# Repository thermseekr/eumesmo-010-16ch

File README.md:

# eumesmo-010-16ch
ESP32 based board with 16x 0-10V analog output, for light dimming control. The board has a DC-DC Converter and an I2C isolator to keep the digital and analog domains fully separated.

The board is compatible with the SP7 DIN rail system from Metaltex.

## VERSION HISTORY
2026-09-22 V1.0 - RJ45 jack and terminal blocks repositioned inwards the board to make space for the PCB holder. ETH tracks rerouted for better EMC.

2026-07-02 V1.0 - Initial release.

## LICENSE

This project is licensed under the [Creative Commons BY-NC 4.0 License](https://creativecommons.org/licenses/by-nc/4.0/).
Commercial use is not permitted without prior written consent. See the [LICENSE.txt](LICENSE.txt) file for details.

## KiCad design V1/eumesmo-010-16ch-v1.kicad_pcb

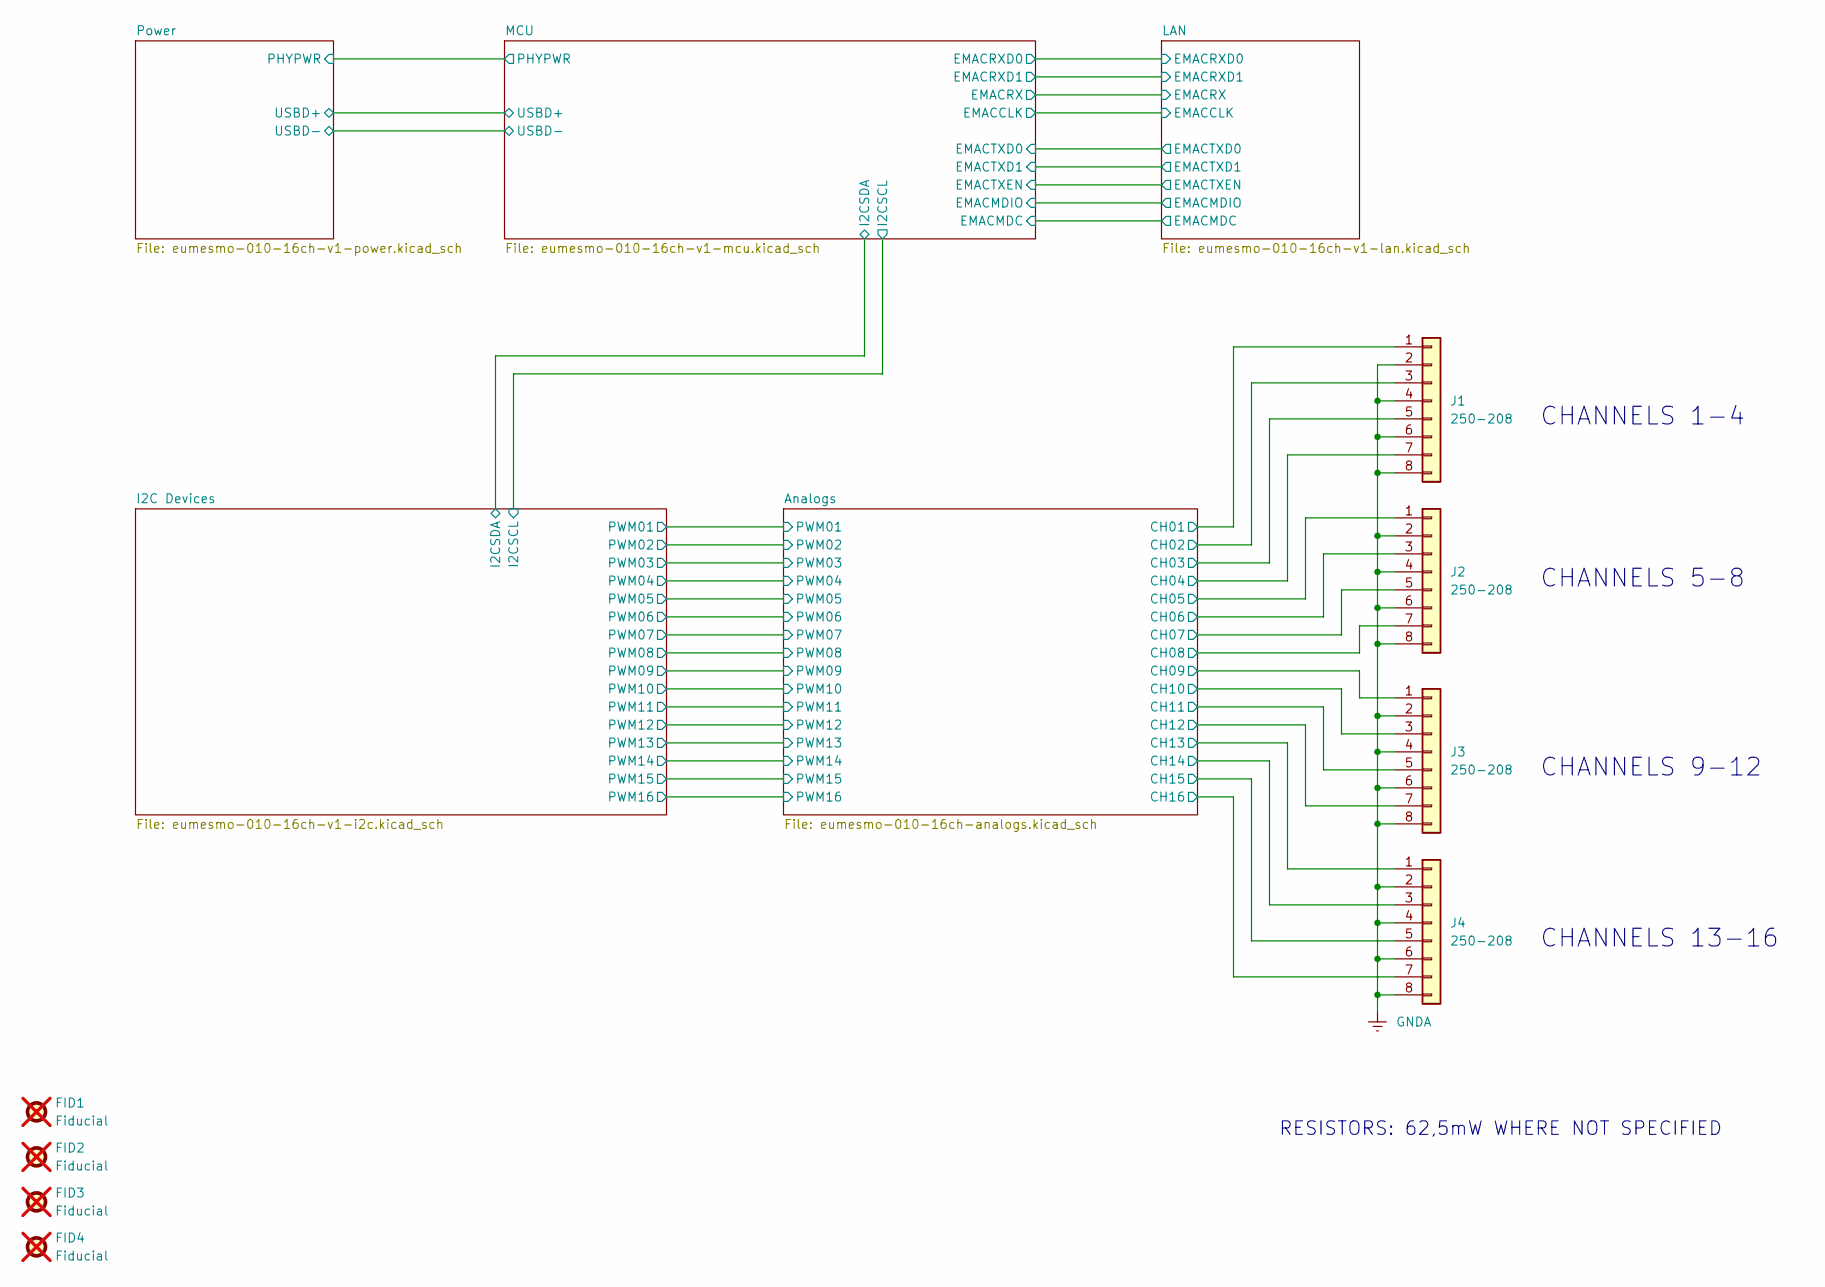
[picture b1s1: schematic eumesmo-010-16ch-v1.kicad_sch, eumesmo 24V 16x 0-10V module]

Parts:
FID1, FID2, FID3, FID4: Fiducial; Fiducial_1mm_Mask2mm; not fitted
J1, J2, J3, J4: 250-208; TerminalBlock_Wago_250-208_1x08_P3.5mm_45Degree; Mfr PN 250-208; LCSC Part # C2833587

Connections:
/Analogs/CH01: J1.1; also elsewhere on the board
/Analogs/CH02: J1.3; also elsewhere on the board
/Analogs/CH03: J1.5; also elsewhere on the board
/Analogs/CH04: J1.7; also elsewhere on the board
/Analogs/CH05: J2.1; also elsewhere on the board
/Analogs/CH06: J2.3; also elsewhere on the board
/Analogs/CH07: J2.5; also elsewhere on the board
/Analogs/CH08: J2.7; also elsewhere on the board
/Analogs/CH09: J3.1; also elsewhere on the board
/Analogs/CH10: J3.3; also elsewhere on the board
/Analogs/CH11: J3.5; also elsewhere on the board
/Analogs/CH12: J3.7; also elsewhere on the board
/Analogs/CH13: J4.1; also elsewhere on the board
/Analogs/CH14: J4.3; also elsewhere on the board
/Analogs/CH15: J4.5; also elsewhere on the board
/Analogs/CH16: J4.7; also elsewhere on the board
GNDA: J1.2, J1.4, J1.6, J1.8, J2.2, J2.4, J2.6, J2.8, J3.2, J3.4, J3.6, J3.8, J4.2, J4.4, J4.6, J4.8; also elsewhere on the board

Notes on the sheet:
CHANNELS 9-12
CHANNELS 13-16
RESISTORS: 62,5mW WHERE NOT SPECIFIED
CHANNELS 1-4
CHANNELS 5-8

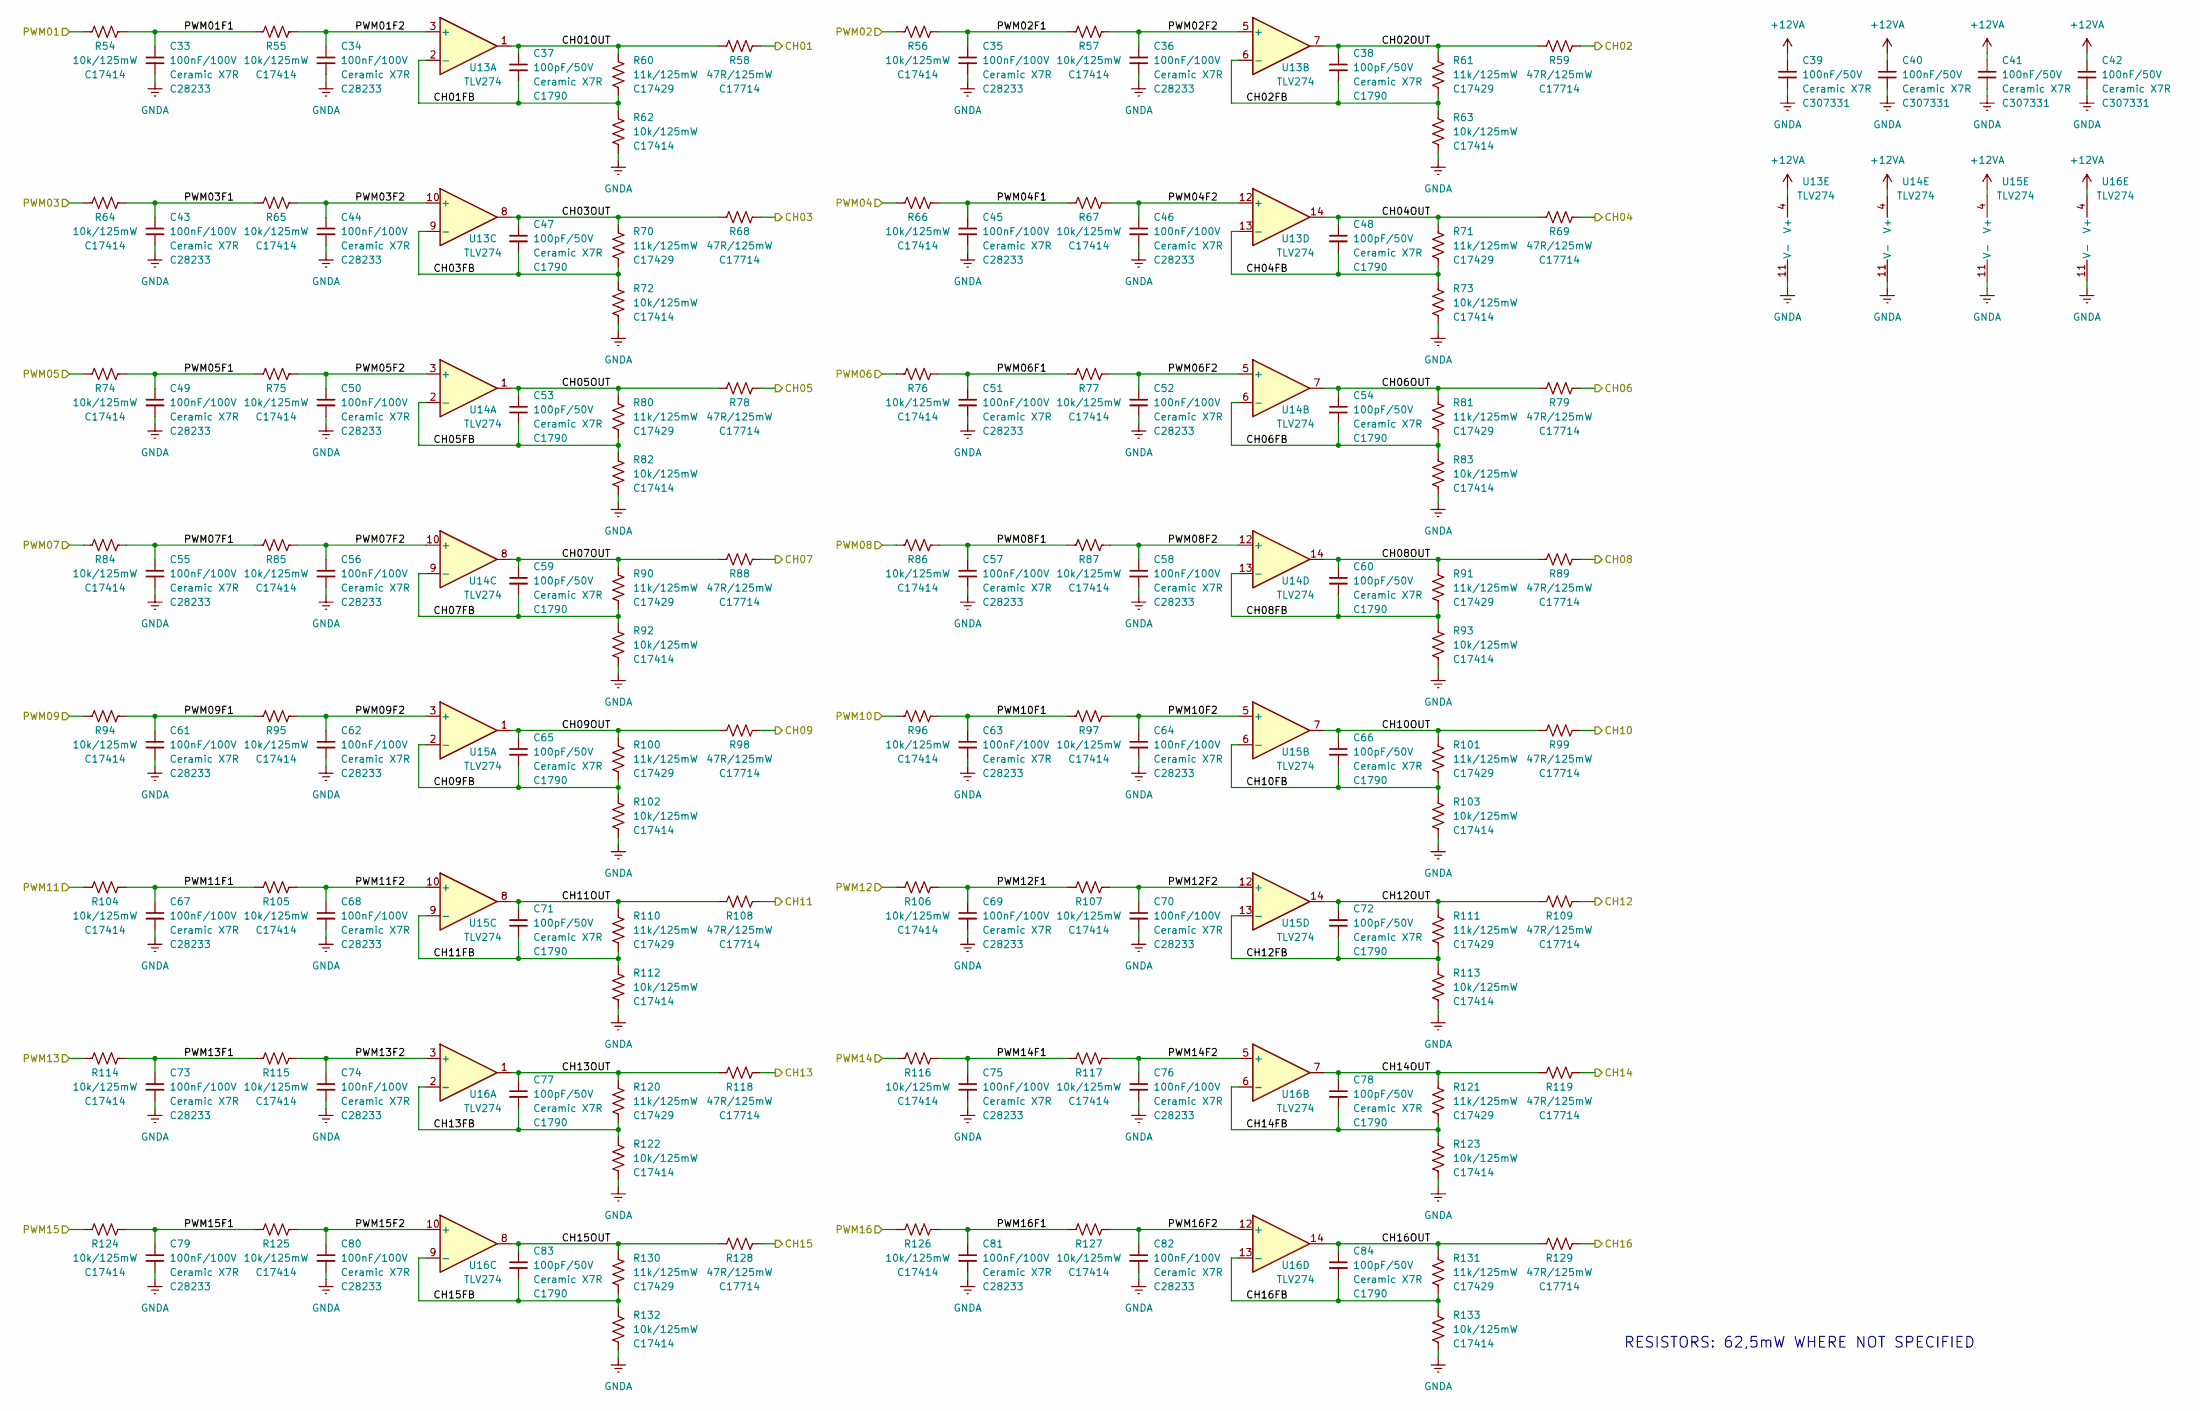
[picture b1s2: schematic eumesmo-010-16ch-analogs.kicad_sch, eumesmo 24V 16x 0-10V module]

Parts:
C33, C34, C35, C36, C43, C44, C45, C46, C49, C50, C51, C52, C55, C56, C57, C58, C61, C62, C63, C64, C67, C68, C69, C70, C73, C74, C75, C76, C79, C80, C81, C82: 100nF/100V; C_0805_2012Metric; Mfr PN CL21B104KCFNNNE; LCSC Part # C28233
C37, C38, C47, C48, C53, C54, C59, C60, C65, C66, C71, C72, C77, C78, C83, C84: 100pF/50V; C_0805_2012Metric; Mfr PN CL21C101JBANNNC; LCSC Part # C1790
C39, C40, C41, C42: 100nF/50V; C_0402_1005Metric; Mfr PN CL05B104KB54PNC; LCSC Part # C307331
R54, R55, R56, R57, R62, R63, R64, R65, R66, R67, R72, R73, R74, R75, R76, R77, R82, R83, R84, R85, R86, R87, R92, R93, R94, R95, R96, R97, R102, R103, R104, R105, R106, R107, R112, R113, R114, R115, R116, R117, R122, R123, R124, R125, R126, R127, R132, R133: 10k/125mW; R_0805_2012Metric; Mfr PN 0805W8F1002T5E; LCSC Part # C17414
R58, R59, R68, R69, R78, R79, R88, R89, R98, R99, R108, R109, R118, R119, R128, R129: 47R/125mW; R_0805_2012Metric; Mfr PN 0805W8F470JT5E; LCSC Part # C17714
R60, R61, R70, R71, R80, R81, R90, R91, R100, R101, R110, R111, R120, R121, R130, R131: 11k/125mW; R_0805_2012Metric; Mfr PN 0805W8F1102T5E; LCSC Part # C17429
U13, U14, U15, U16: TLV274; TSSOP-14_4.4x5mm_P0.65mm; Mfr PN TLV274; LCSC Part # C9914

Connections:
+12VA: C39.1, C40.1, C41.1, C42.1, U13.4 (V+), U14.4 (V+), U15.4 (V+), U16.4 (V+); also elsewhere on the board
/Analogs/CH01: R58.2; also elsewhere on the board
/Analogs/CH01FB: C37.2, R60.1, R62.2, U13.2 (-)
/Analogs/CH01OUT: C37.1, R58.1, R60.2, U13.1
/Analogs/CH02: R59.2; also elsewhere on the board
/Analogs/CH02FB: C38.2, R61.1, R63.2, U13.6 (-)
/Analogs/CH02OUT: C38.1, R59.1, R61.2, U13.7
/Analogs/CH03: R68.2; also elsewhere on the board
/Analogs/CH03FB: C47.2, R70.1, R72.2, U13.9 (-)
/Analogs/CH03OUT: C47.1, R68.1, R70.2, U13.8
/Analogs/CH04: R69.2; also elsewhere on the board
/Analogs/CH04FB: C48.2, R71.1, R73.2, U13.13 (-)
/Analogs/CH04OUT: C48.1, R69.1, R71.2, U13.14
/Analogs/CH05: R78.2; also elsewhere on the board
/Analogs/CH05FB: C53.2, R80.1, R82.2, U14.2 (-)
/Analogs/CH05OUT: C53.1, R78.1, R80.2, U14.1
/Analogs/CH06: R79.2; also elsewhere on the board
/Analogs/CH06FB: C54.2, R81.1, R83.2, U14.6 (-)
/Analogs/CH06OUT: C54.1, R79.1, R81.2, U14.7
/Analogs/CH07: R88.2; also elsewhere on the board
/Analogs/CH07FB: C59.2, R90.1, R92.2, U14.9 (-)
/Analogs/CH07OUT: C59.1, R88.1, R90.2, U14.8
/Analogs/CH08: R89.2; also elsewhere on the board
/Analogs/CH08FB: C60.2, R91.1, R93.2, U14.13 (-)
/Analogs/CH08OUT: C60.1, R89.1, R91.2, U14.14
/Analogs/CH09: R98.2; also elsewhere on the board
/Analogs/CH09FB: C65.2, R100.1, R102.2, U15.2 (-)
/Analogs/CH09OUT: C65.1, R98.1, R100.2, U15.1
/Analogs/CH10: R99.2; also elsewhere on the board
/Analogs/CH10FB: C66.2, R101.1, R103.2, U15.6 (-)
/Analogs/CH10OUT: C66.1, R99.1, R101.2, U15.7
/Analogs/CH11: R108.2; also elsewhere on the board
/Analogs/CH11FB: C71.2, R110.1, R112.2, U15.9 (-)
/Analogs/CH11OUT: C71.1, R108.1, R110.2, U15.8
/Analogs/CH12: R109.2; also elsewhere on the board
/Analogs/CH12FB: C72.2, R111.1, R113.2, U15.13 (-)
/Analogs/CH12OUT: C72.1, R109.1, R111.2, U15.14
/Analogs/CH13: R118.2; also elsewhere on the board
/Analogs/CH13FB: C77.2, R120.1, R122.2, U16.2 (-)
/Analogs/CH13OUT: C77.1, R118.1, R120.2, U16.1
/Analogs/CH14: R119.2; also elsewhere on the board
/Analogs/CH14FB: C78.2, R121.1, R123.2, U16.6 (-)
/Analogs/CH14OUT: C78.1, R119.1, R121.2, U16.7
/Analogs/CH15: R128.2; also elsewhere on the board
/Analogs/CH15FB: C83.2, R130.1, R132.2, U16.9 (-)
/Analogs/CH15OUT: C83.1, R128.1, R130.2, U16.8
/Analogs/CH16: R129.2; also elsewhere on the board
/Analogs/CH16FB: C84.2, R131.1, R133.2, U16.13 (-)
/Analogs/CH16OUT: C84.1, R129.1, R131.2, U16.14
/Analogs/PWM01: R54.1; also elsewhere on the board
/Analogs/PWM01F1: C33.1, R54.2, R55.1
/Analogs/PWM01F2: C34.1, R55.2, U13.3 (+)
/Analogs/PWM02: R56.1; also elsewhere on the board
/Analogs/PWM02F1: C35.1, R56.2, R57.1
/Analogs/PWM02F2: C36.1, R57.2, U13.5 (+)
/Analogs/PWM03: R64.1; also elsewhere on the board
/Analogs/PWM03F1: C43.1, R64.2, R65.1
/Analogs/PWM03F2: C44.1, R65.2, U13.10 (+)
/Analogs/PWM04: R66.1; also elsewhere on the board
/Analogs/PWM04F1: C45.1, R66.2, R67.1
/Analogs/PWM04F2: C46.1, R67.2, U13.12 (+)
/Analogs/PWM05: R74.1; also elsewhere on the board
/Analogs/PWM05F1: C49.1, R74.2, R75.1
/Analogs/PWM05F2: C50.1, R75.2, U14.3 (+)
/Analogs/PWM06: R76.1; also elsewhere on the board
/Analogs/PWM06F1: C51.1, R76.2, R77.1
/Analogs/PWM06F2: C52.1, R77.2, U14.5 (+)
/Analogs/PWM07: R84.1; also elsewhere on the board
/Analogs/PWM07F1: C55.1, R84.2, R85.1
/Analogs/PWM07F2: C56.1, R85.2, U14.10 (+)
/Analogs/PWM08: R86.1; also elsewhere on the board
/Analogs/PWM08F1: C57.1, R86.2, R87.1
/Analogs/PWM08F2: C58.1, R87.2, U14.12 (+)
/Analogs/PWM09: R94.1; also elsewhere on the board
/Analogs/PWM09F1: C61.1, R94.2, R95.1
/Analogs/PWM09F2: C62.1, R95.2, U15.3 (+)
/Analogs/PWM10: R96.1; also elsewhere on the board
/Analogs/PWM10F1: C63.1, R96.2, R97.1
/Analogs/PWM10F2: C64.1, R97.2, U15.5 (+)
/Analogs/PWM11: R104.1; also elsewhere on the board
/Analogs/PWM11F1: C67.1, R104.2, R105.1
/Analogs/PWM11F2: C68.1, R105.2, U15.10 (+)
/Analogs/PWM12: R106.1; also elsewhere on the board
/Analogs/PWM12F1: C69.1, R106.2, R107.1
/Analogs/PWM12F2: C70.1, R107.2, U15.12 (+)
/Analogs/PWM13: R114.1; also elsewhere on the board
/Analogs/PWM13F1: C73.1, R114.2, R115.1
/Analogs/PWM13F2: C74.1, R115.2, U16.3 (+)
/Analogs/PWM14: R116.1; also elsewhere on the board
/Analogs/PWM14F1: C75.1, R116.2, R117.1
/Analogs/PWM14F2: C76.1, R117.2, U16.5 (+)
/Analogs/PWM15: R124.1; also elsewhere on the board
/Analogs/PWM15F1: C79.1, R124.2, R125.1
/Analogs/PWM15F2: C80.1, R125.2, U16.10 (+)
/Analogs/PWM16: R126.1; also elsewhere on the board
/Analogs/PWM16F1: C81.1, R126.2, R127.1
/Analogs/PWM16F2: C82.1, R127.2, U16.12 (+)
GNDA: C33.2, C34.2, C35.2, C36.2, C39.2, C40.2, C41.2, C42.2, C43.2, C44.2, C45.2, C46.2, C49.2, C50.2, C51.2, C52.2, C55.2, C56.2, C57.2, C58.2, C61.2, C62.2, C63.2, C64.2, C67.2, C68.2, C69.2, C70.2, C73.2, C74.2, C75.2, C76.2, C79.2, C80.2, C81.2, C82.2, R62.1, R63.1, R72.1, R73.1, R82.1, R83.1, R92.1, R93.1, R102.1, R103.1, R112.1, R113.1, R122.1, R123.1, R132.1, R133.1, U13.11 (V-), U14.11 (V-), U15.11 (V-), U16.11 (V-); also elsewhere on the board

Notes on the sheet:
RESISTORS: 62,5mW WHERE NOT SPECIFIED

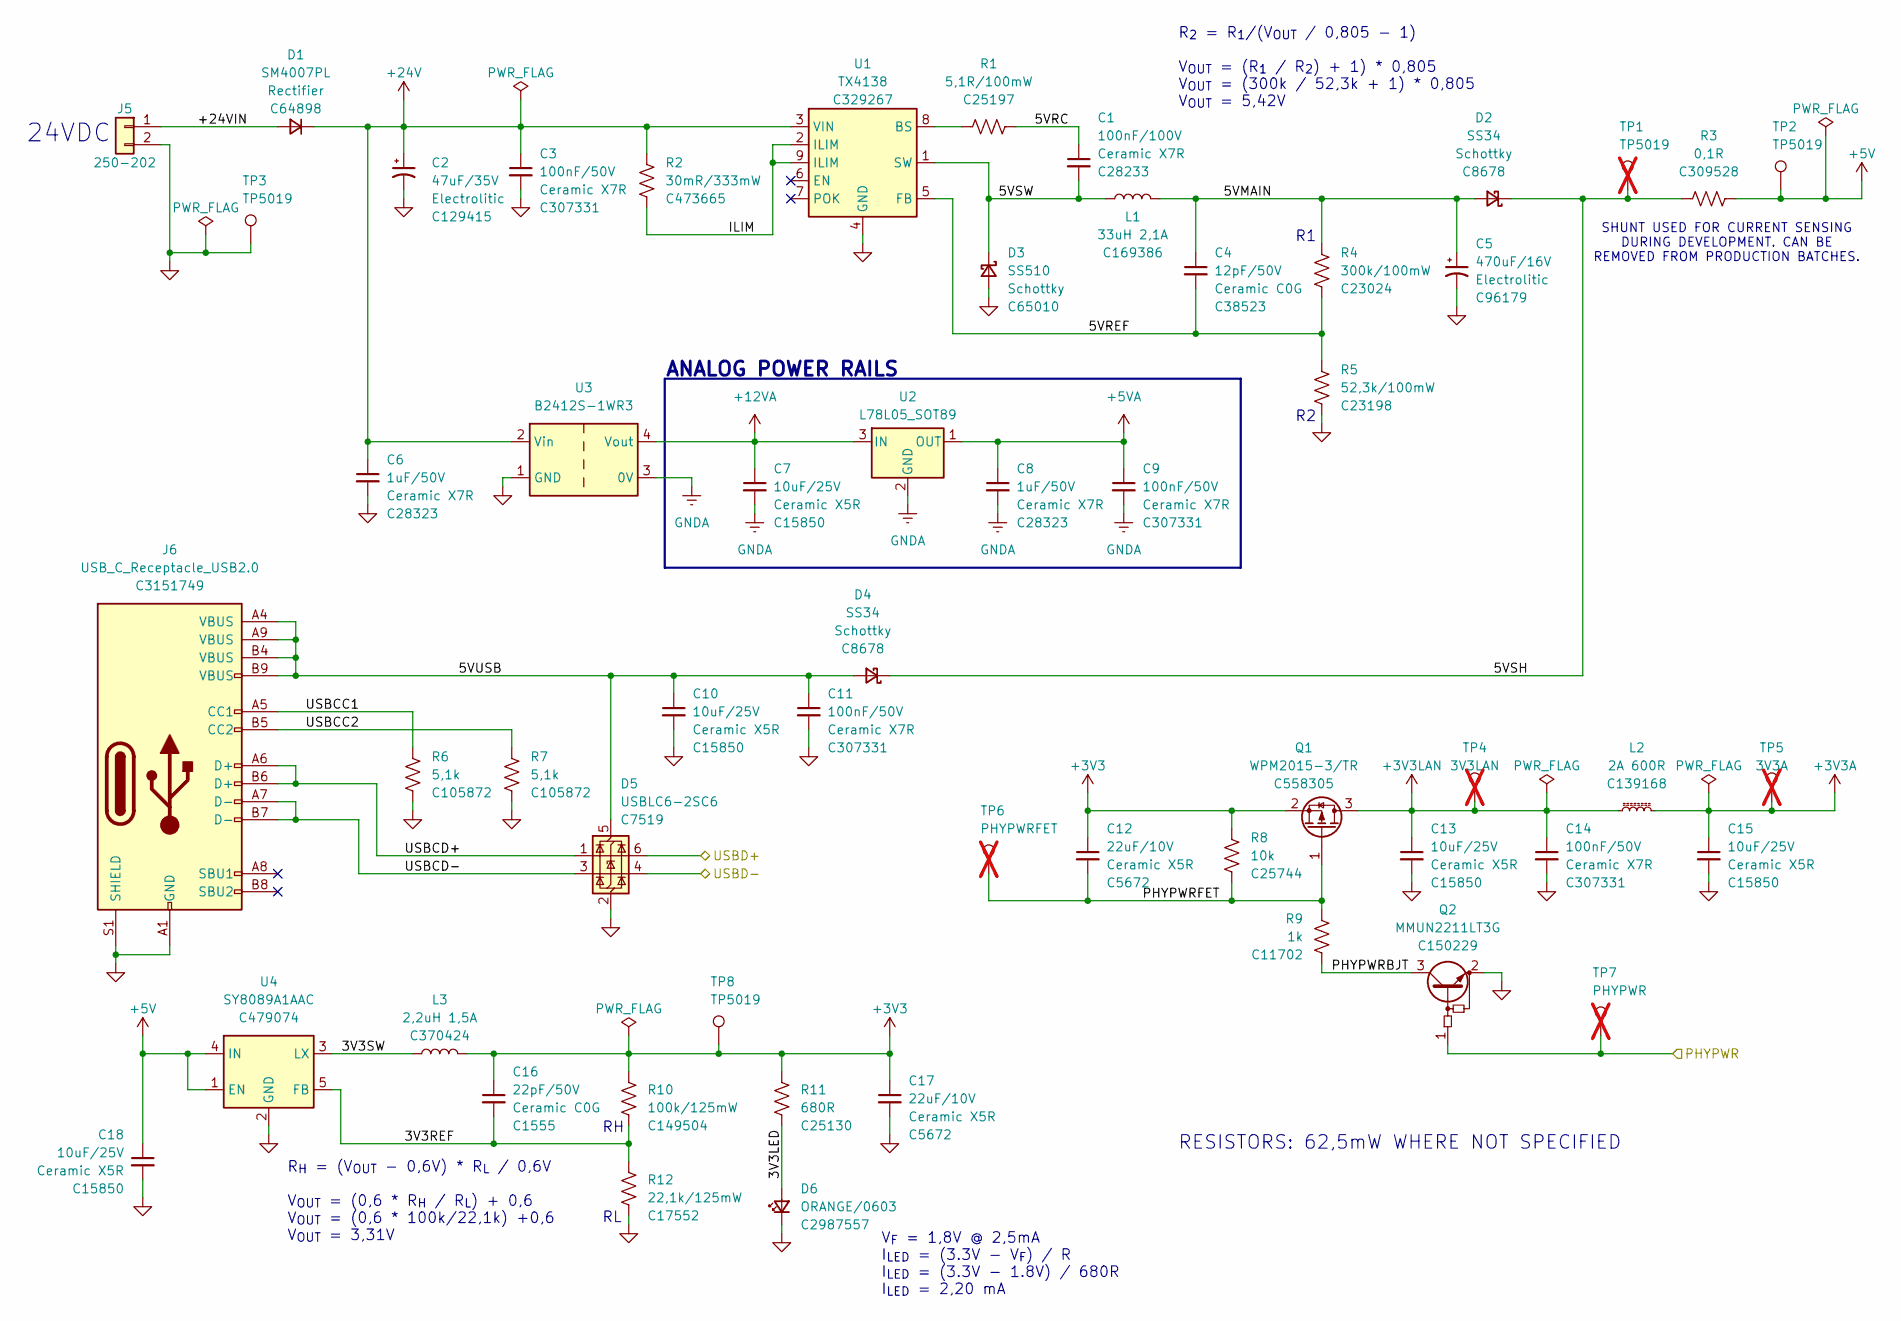
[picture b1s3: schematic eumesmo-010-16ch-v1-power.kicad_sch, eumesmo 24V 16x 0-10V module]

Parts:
C1: 100nF/100V; C_0805_2012Metric; Mfr PN CL21B104KCFNNNE; LCSC Part # C28233
C2: 47uF/35V; CP_Elec_6.3x5.4; Mfr PN CK1V470M-CRE54; LCSC Part # C129415
C3, C9, C11, C14: 100nF/50V; C_0402_1005Metric; Mfr PN CL05B104KB54PNC; LCSC Part # C307331
C4: 12pF/50V; C_0603_1608Metric; Mfr PN CL10C120JB8NNNC; LCSC Part # C38523
C5: 470uF/16V; CP_Elec_8x10.5; Mfr PN CS1C471M-CRF10; LCSC Part # C96179
C6, C8: 1uF/50V; C_0805_2012Metric; Mfr PN CL21B105KBFNNNE; LCSC Part # C28323
C7, C10, C13, C15, C18: 10uF/25V; C_0805_2012Metric; Mfr PN CL21A106KAYNNNE; LCSC Part # C15850
C12, C17: 22uF/10V; C_1206_3216Metric; Mfr PN CL31A226KPHNNNE; LCSC Part # C5672
C16: 22pF/50V; C_0402_1005Metric; Mfr PN 0402CG220J500NT; LCSC Part # C1555
D1: SM4007PL; D_SOD-123; Mfr PN SM4007PL; LCSC Part # C64898
D2, D4: SS34; D_SMA; Mfr PN SS34; LCSC Part # C8678
D3: SS510; D_SMA; Mfr PN SS510; LCSC Part # C65010
D5: USBLC6-2SC6; SOT-23-6; Mfr PN USBLC6-2SC6; LCSC Part # C7519
D6: ORANGE/0603; LED_0603_1608Metric; Mfr PN 19-217/S2C-AL1M2VY/6T; LCSC Part # C2987557
J5: 250-202; TerminalBlock_Wago_250-202_1x02_P3.5mm_45Degree; Mfr PN 250-202; LCSC Part # C2765061
J6: USB_C_Receptacle_USB2.0; USB_C_Receptacle_ShouHan_TYPE-C-16PLT-H10.0; Mfr PN TYPE-C 16PLT-H10.0; LCSC Part # C3151749
L1: 33uH 2,1A; L_12x12mm_H6mm; Mfr PN SWRB1205S-330MT; LCSC Part # C169386
L2: 2A 600R; L_0805_2012Metric; Mfr PN CBM201209U601T; LCSC Part # C139168
L3: 2,2uH 1,5A; L_3x3mm_H1.5mm; Mfr PN SPH3015H2R2MT; LCSC Part # C370424
Q1: WPM2015-3/TR; SOT-23; Mfr PN WPM2015-3/TR; LCSC Part # C558305
Q2: MMUN2211LT3G; SOT-23; Mfr PN MMUN2211LT3G; LCSC Part # C150229
R1: 5,1R/100mW; R_0603_1608Metric; Mfr PN 0603WAF510KT5E; LCSC Part # C25197
R2: 30mR/333mW; R_1206_3216Metric; Mfr PN 1206W3F300MT5E; LCSC Part # C473665
R3: 0,1R; C_1206_3216Metric; Mfr PN PE1206FRF470R1L; LCSC Part # C309528
R4: 300k/100mW; R_0603_1608Metric; Mfr PN 0603WAF3003T5E; LCSC Part # C23024
R5: 52,3k/100mW; R_0603_1608Metric; Mfr PN 0603WAF5232T5E; LCSC Part # C23198
R6, R7: 5,1k; R_0402_1005Metric; Mfr PN RC0402FR-075K1L; LCSC Part # C105872
R8: 10k; R_0402_1005Metric; Mfr PN 0402WGF1002TCE; LCSC Part # C25744
R9: 1k; R_0402_1005Metric; Mfr PN 0402WGF1001TCE; LCSC Part # C11702
R10: 100k/125mW; R_0805_2012Metric; Mfr PN 0805W8F1003T5E; LCSC Part # C149504
R11: 680R; R_0402_1005Metric; Mfr PN 0402WGF6800TCE; LCSC Part # C25130
R12: 22,1k/125mW; R_0805_2012Metric; Mfr PN 0805W8F2212T5E; LCSC Part # C17552
TP1: TP5019; TestPoint_Keystone_5019_Miniature; Mfr PN 5019; LCSC Part # C238131; not fitted
TP2, TP3, TP8: TP5019; TestPoint_Keystone_5019_Miniature; Mfr PN 5019; LCSC Part # C238131
TP4: 3V3LAN; TestPoint_Pad_D1.5mm; not fitted
TP5: 3V3A; TestPoint_Pad_D1.5mm; not fitted
TP6: PHYPWRFET; TestPoint_Pad_D1.5mm; not fitted
TP7: PHYPWR; TestPoint_Pad_D1.5mm; not fitted
U1: TX4138; SOIC-8-1EP_3.9x4.9mm_P1.27mm_EP2.41x3.81mm_ThermalVias; Mfr PN TX4138; LCSC Part # C329267
U2: L78L05_SOT89; SOT-89-3; Mfr PN L78L05ABUTR; LCSC Part # C42738
U3: B2412S-1WR3; Ylptec BxxxxS-1WR3; Mfr PN B2412S-1WR3; LCSC Part # C5369469
U4: SY8089A1AAC; SOT-23-5_Shorter_Pins; Mfr PN SY8089A1AAC; LCSC Part # C479074

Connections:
+3V3: C12.1, C16.1, C17.1, L3.2, Q1.2 (S), R8.1, R10.1, R11.1, TP8.1 (1_1); also elsewhere on the board
+3V3A: C15.1, L2.2, TP5.1; also elsewhere on the board
+3V3LAN: C13.1, C14.1, L2.1, Q1.3 (D), TP4.1; also elsewhere on the board
+5V: C18.1, R3.1, TP2.1 (1_1), U4.1 (EN), U4.4 (IN)
+5VA: C8.1, C9.1, U2.1 (OUT); also elsewhere on the board
+12VA: C7.1, U2.3 (IN), U3.4 (Vout); also elsewhere on the board
+24V: C2.1, C3.1, C6.1, D1.1 (K), R2.1, U1.3 (VIN), U3.2 (Vin)
/MCU/PHYPWR: Q2.1 (B), TP7.1; also elsewhere on the board
/MCU/USBD+: D5.6 (I/O1); also elsewhere on the board
/MCU/USBD-: D5.4 (I/O2); also elsewhere on the board
/Power/3V3LED: D6.2 (A), R11.2
/Power/3V3REF: C16.2, R10.2, R12.1, U4.5 (FB)
/Power/3V3SW: L3.1, U4.3 (LX)
/Power/5VMAIN: C4.1, C5.1, D2.2 (A), L1.2, R4.1
/Power/5VRC: C1.1, R1.1
/Power/5VREF: C4.2, R4.2, R5.1, U1.5 (FB)
/Power/5VSH: D2.1 (K), D4.1 (K), R3.2, TP1.1
/Power/5VSW: C1.2, D3.1 (K), L1.1, U1.1 (SW)
/Power/5VUSB: C10.1, C11.1, D4.2 (A), D5.5 (VBUS), J6.A4 (VBUS), J6.A9 (VBUS), J6.B4 (VBUS), J6.B9 (VBUS)
/Power/+24VIN: D1.2 (A), J5.1
/Power/ILIM: R2.2, U1.2 (ILIM), U1.9 (ILIM)
/Power/PHYPWRBJT: Q2.3 (C), R9.1
/Power/PHYPWRFET: C12.2, Q1.1 (G), R8.2, R9.2, TP6.1
/Power/USBCC1: J6.A5 (CC1), R6.1
/Power/USBCC2: J6.B5 (CC2), R7.1
/Power/USBCD+: D5.1 (I/O1), J6.A6 (D+), J6.B6 (D+)
/Power/USBCD-: D5.3 (I/O2), J6.A7 (D-), J6.B7 (D-)
GND: C2.2, C3.2, C5.2, C6.2, C10.2, C11.2, C13.2, C14.2, C15.2, C17.2, C18.2, D3.2 (A), D5.2 (GND), D6.1 (K), J5.2, J6.A1 (GND), J6.A12 (GND), J6.B1 (GND), J6.B12 (GND), J6.S1 (SHIELD), Q2.2 (E), R5.2, R6.2, R7.2, R12.2, TP3.1 (1_1), U1.4 (GND), U3.1 (GND), U4.2 (GND); also elsewhere on the board
GNDA: C7.2, C8.2, C9.2, U2.2 (GND), U3.3 (0V); also elsewhere on the board
unnamed: R1.2, U1.8 (BS)

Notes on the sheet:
RESISTORS: 62,5mW WHERE NOT SPECIFIED
R_{H} = (V_{OUT} - 0,6V) * R_{L} / 0,6V V_{OUT} = (0,6 * R_{H} / R_{L}) + 0,6 V_{OUT} = (0,6 * 100k/22,1k) +0,6 V_{OUT} = 3,31V
R_{2} = R_{1}/(V_{OUT} / 0,805 - 1) V_{OUT} = (R_{1} / R_{2}) + 1) * 0,805 V_{OUT} = (300k / 52,3k + 1) * 0,805 V_{OUT} = 5,42V
SHUNT USED FOR CURRENT SENSING DURING DEVELOPMENT. CAN BE REMOVED FROM PRODUCTION BATCHES.
V_{F} = 1,8V @ 2,5mA I_{LED} = (3.3V - V_{F}) / R I_{LED} = (3.3V - 1.8V) / 680R I_{LED} = 2,20 mA
ANALOG POWER RAILS
24VDC

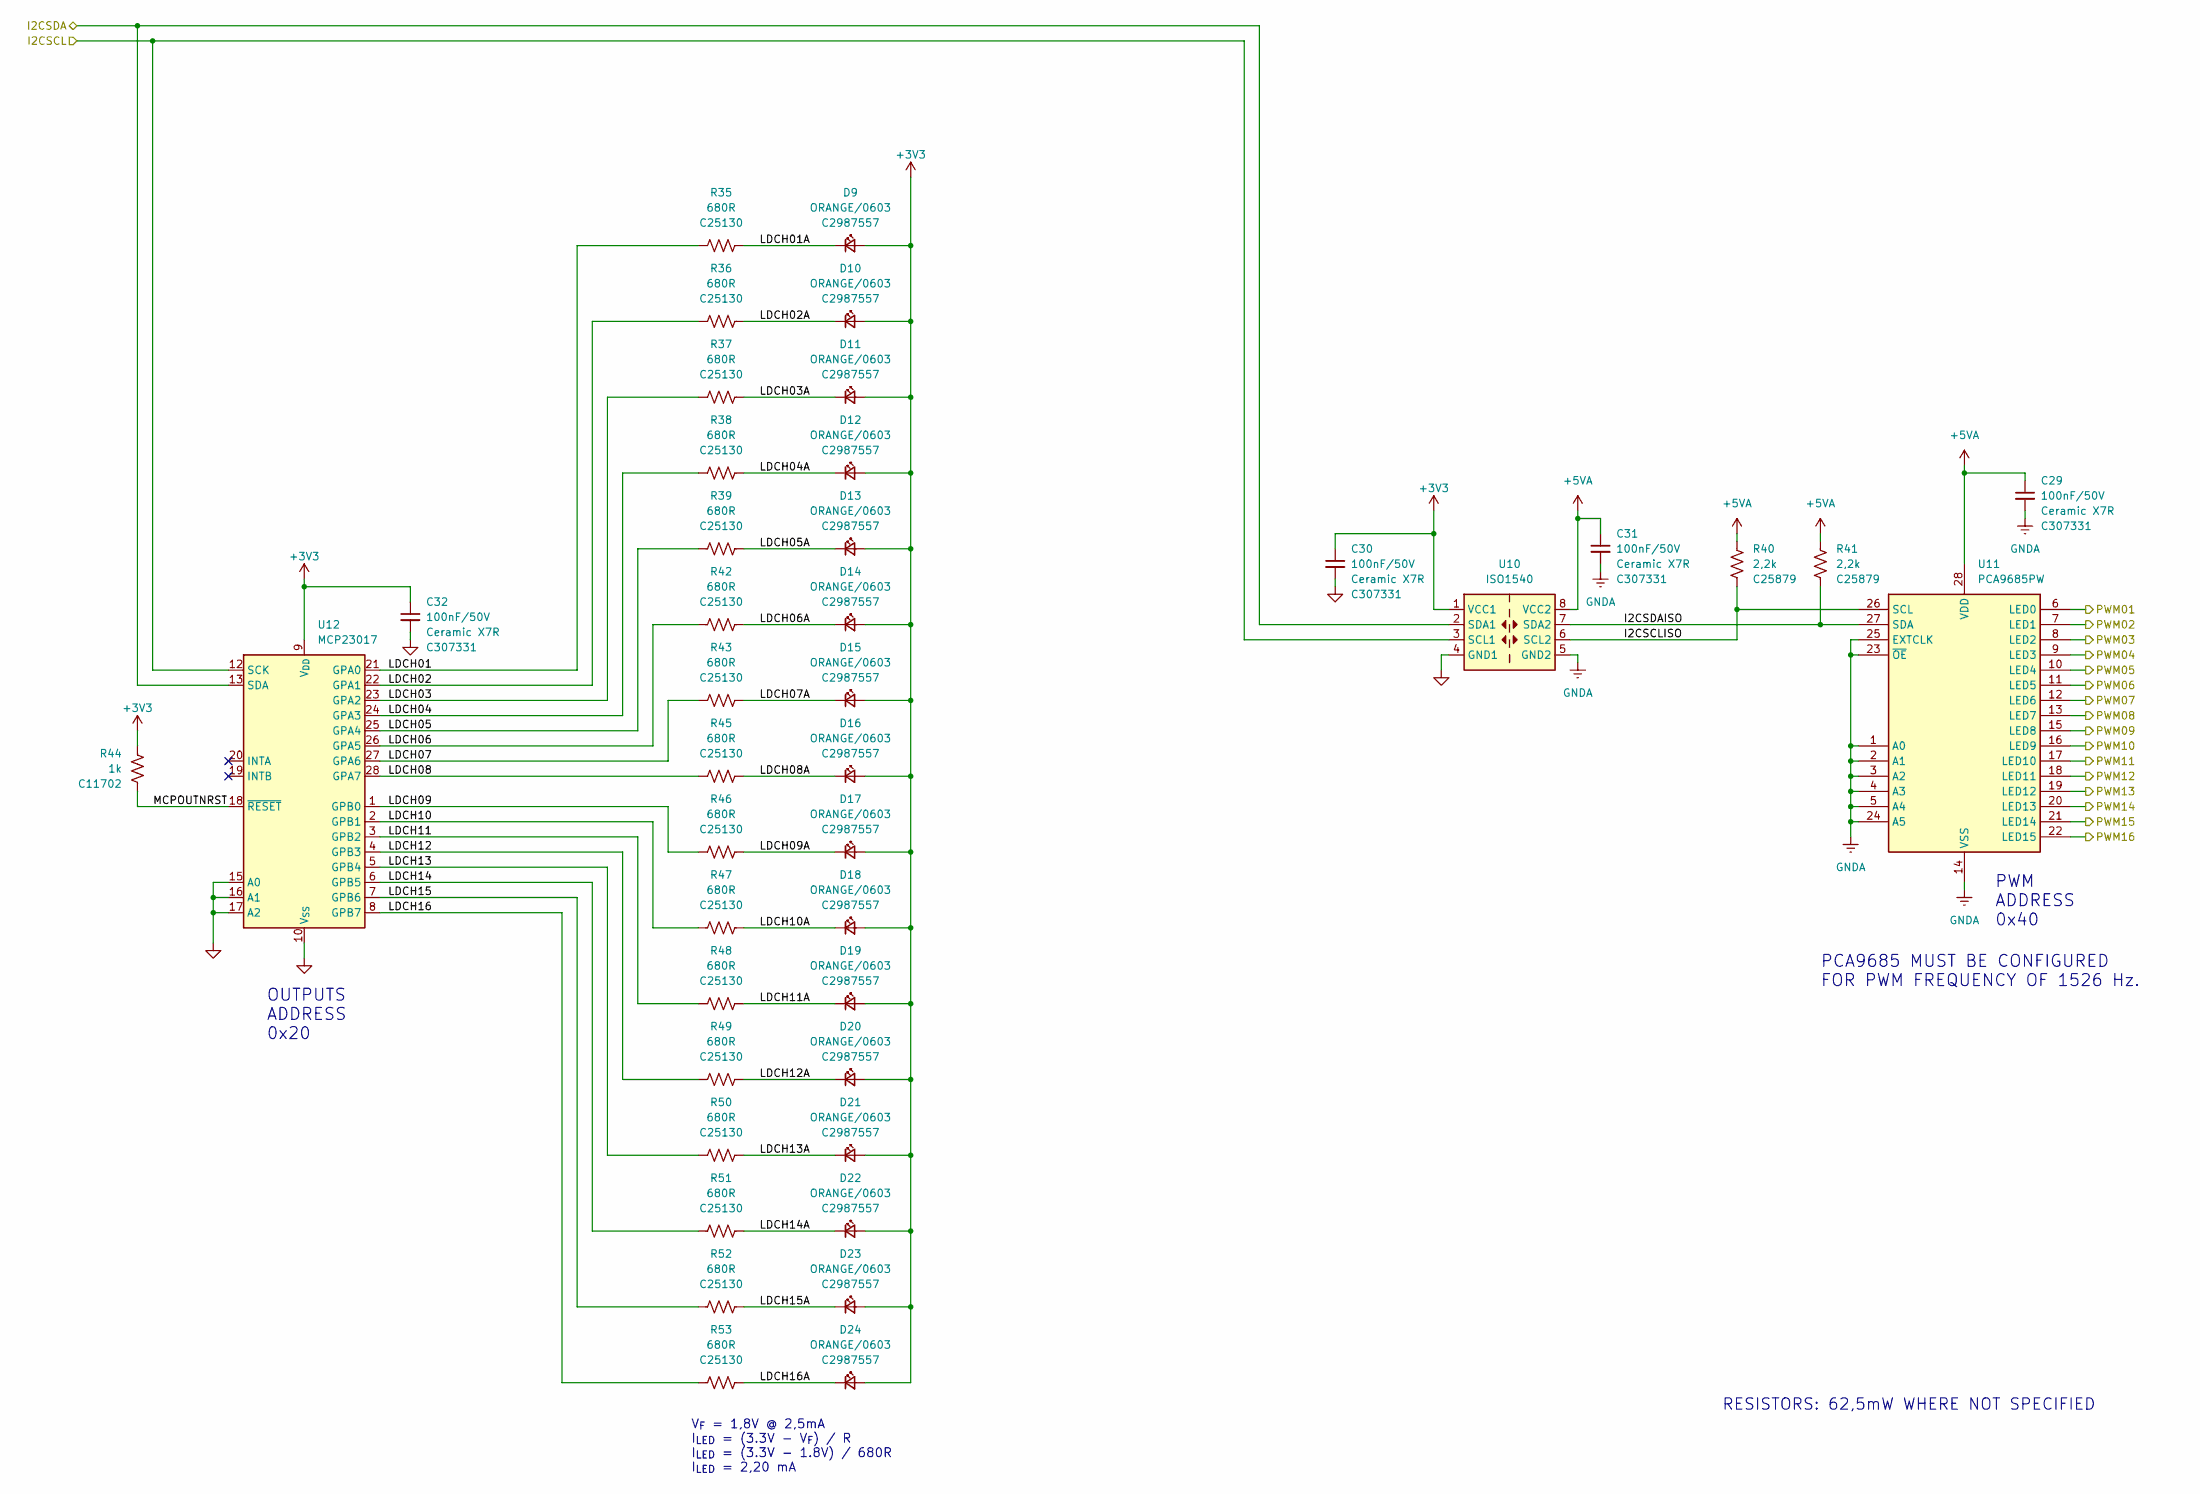
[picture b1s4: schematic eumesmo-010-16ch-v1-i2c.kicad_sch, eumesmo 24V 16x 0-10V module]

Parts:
C29, C30, C31, C32: 100nF/50V; C_0402_1005Metric; Mfr PN CL05B104KB54PNC; LCSC Part # C307331
D9, D10, D11, D12, D13, D14, D15, D16, D17, D18, D19, D20, D21, D22, D23, D24: ORANGE/0603; LED_0603_1608Metric; Mfr PN 19-217/S2C-AL1M2VY/6T; LCSC Part # C2987557
R35, R36, R37, R38, R39, R42, R43, R45, R46, R47, R48, R49, R50, R51, R52, R53: 680R; R_0402_1005Metric; Mfr PN 0402WGF6800TCE; LCSC Part # C25130
R40, R41: 2,2k; R_0402_1005Metric; Mfr PN 0402WGF2201TCE; LCSC Part # C25879
R44: 1k; R_0402_1005Metric; Mfr PN 0402WGF1001TCE; LCSC Part # C11702
U10: ISO1540; SOIC-8_3.9x4.9mm_P1.27mm; Mfr PN ISO1540DR; LCSC Part # C179739
U11: PCA9685PW; TSSOP-28_4.4x9.7mm_P0.65mm; Mfr PN PCA9685PW; LCSC Part # C2678753
U12: MCP23017; SSOP-28_5.3x10.2mm_P0.65mm; Mfr PN MCP23017-E/SS; LCSC Part # C506653

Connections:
+3V3: C30.1, C32.1, D9.2 (A), D10.2 (A), D11.2 (A), D12.2 (A), D13.2 (A), D14.2 (A), D15.2 (A), D16.2 (A), D17.2 (A), D18.2 (A), D19.2 (A), D20.2 (A), D21.2 (A), D22.2 (A), D23.2 (A), D24.2 (A), R44.1, U10.1 (VCC1), U12.9 (V_{DD}); also elsewhere on the board
+5VA: C29.1, C31.1, R40.1, R41.1, U10.8 (VCC2), U11.28 (VDD); also elsewhere on the board
/Analogs/PWM01: U11.6 (LED0); also elsewhere on the board
/Analogs/PWM02: U11.7 (LED1); also elsewhere on the board
/Analogs/PWM03: U11.8 (LED2); also elsewhere on the board
/Analogs/PWM04: U11.9 (LED3); also elsewhere on the board
/Analogs/PWM05: U11.10 (LED4); also elsewhere on the board
/Analogs/PWM06: U11.11 (LED5); also elsewhere on the board
/Analogs/PWM07: U11.12 (LED6); also elsewhere on the board
/Analogs/PWM08: U11.13 (LED7); also elsewhere on the board
/Analogs/PWM09: U11.15 (LED8); also elsewhere on the board
/Analogs/PWM10: U11.16 (LED9); also elsewhere on the board
/Analogs/PWM11: U11.17 (LED10); also elsewhere on the board
/Analogs/PWM12: U11.18 (LED11); also elsewhere on the board
/Analogs/PWM13: U11.19 (LED12); also elsewhere on the board
/Analogs/PWM14: U11.20 (LED13); also elsewhere on the board
/Analogs/PWM15: U11.21 (LED14); also elsewhere on the board
/Analogs/PWM16: U11.22 (LED15); also elsewhere on the board
/I2C Devices/I2CSCL: U10.3 (SCL1), U12.12 (SCK); also elsewhere on the board
/I2C Devices/I2CSCLISO: R40.2, U10.6 (SCL2), U11.26 (SCL)
/I2C Devices/I2CSDA: U10.2 (SDA1), U12.13 (SDA); also elsewhere on the board
/I2C Devices/I2CSDAISO: R41.2, U10.7 (SDA2), U11.27 (SDA)
/I2C Devices/LDCH01: R35.1, U12.21 (GPA0)
/I2C Devices/LDCH01A: D9.1 (K), R35.2
/I2C Devices/LDCH02: R36.1, U12.22 (GPA1)
/I2C Devices/LDCH02A: D10.1 (K), R36.2
/I2C Devices/LDCH03: R37.1, U12.23 (GPA2)
/I2C Devices/LDCH03A: D11.1 (K), R37.2
/I2C Devices/LDCH04: R38.1, U12.24 (GPA3)
/I2C Devices/LDCH04A: D12.1 (K), R38.2
/I2C Devices/LDCH05: R39.1, U12.25 (GPA4)
/I2C Devices/LDCH05A: D13.1 (K), R39.2
/I2C Devices/LDCH06: R42.1, U12.26 (GPA5)
/I2C Devices/LDCH06A: D14.1 (K), R42.2
/I2C Devices/LDCH07: R43.1, U12.27 (GPA6)
/I2C Devices/LDCH07A: D15.1 (K), R43.2
/I2C Devices/LDCH08: R45.1, U12.28 (GPA7)
/I2C Devices/LDCH08A: D16.1 (K), R45.2
/I2C Devices/LDCH09: R46.1, U12.1 (GPB0)
/I2C Devices/LDCH09A: D17.1 (K), R46.2
/I2C Devices/LDCH10: R47.1, U12.2 (GPB1)
/I2C Devices/LDCH10A: D18.1 (K), R47.2
/I2C Devices/LDCH11: R48.1, U12.3 (GPB2)
/I2C Devices/LDCH11A: D19.1 (K), R48.2
/I2C Devices/LDCH12: R49.1, U12.4 (GPB3)
/I2C Devices/LDCH12A: D20.1 (K), R49.2
/I2C Devices/LDCH13: R50.1, U12.5 (GPB4)
/I2C Devices/LDCH13A: D21.1 (K), R50.2
/I2C Devices/LDCH14: R51.1, U12.6 (GPB5)
/I2C Devices/LDCH14A: D22.1 (K), R51.2
/I2C Devices/LDCH15: R52.1, U12.7 (GPB6)
/I2C Devices/LDCH15A: D23.1 (K), R52.2
/I2C Devices/LDCH16: R53.1, U12.8 (GPB7)
/I2C Devices/LDCH16A: D24.1 (K), R53.2
/I2C Devices/MCPOUTNRST: R44.2, U12.18 (~RESET)
GND: C30.2, C32.2, U10.4 (GND1), U12.10 (V_{SS}), U12.15 (A0), U12.16 (A1), U12.17 (A2); also elsewhere on the board
GNDA: C29.2, C31.2, U10.5 (GND2), U11.1 (A0), U11.2 (A1), U11.3 (A2), U11.4 (A3), U11.5 (A4), U11.14 (VSS), U11.23 (~OE), U11.24 (A5), U11.25 (EXTCLK); also elsewhere on the board

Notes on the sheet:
PWM ADDRESS 0x40
OUTPUTS ADDRESS 0x20
V_{F} = 1,8V @ 2,5mA I_{LED} = (3.3V - V_{F}) / R I_{LED} = (3.3V - 1.8V) / 680R I_{LED} = 2,20 mA
RESISTORS: 62,5mW WHERE NOT SPECIFIED
PCA9685 MUST BE CONFIGURED FOR PWM FREQUENCY OF 1526 Hz.
